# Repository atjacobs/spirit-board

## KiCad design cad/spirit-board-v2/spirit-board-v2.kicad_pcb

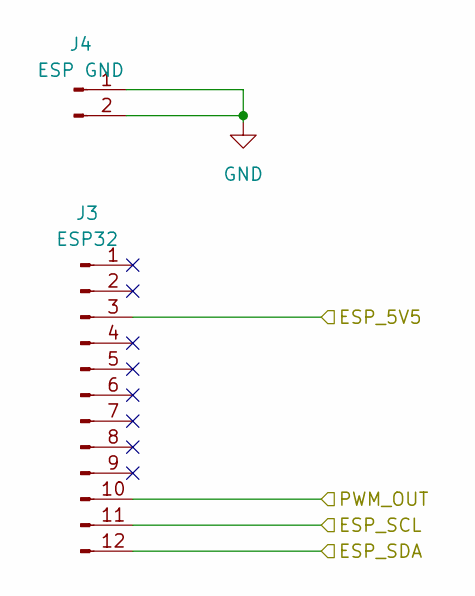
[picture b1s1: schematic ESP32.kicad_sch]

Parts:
J3: ESP32; PinHeader_1x12_P2.54mm_Vertical
J4: ESP GND; PinSocket_1x02_P2.54mm_Vertical

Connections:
/ESP32/ESP_5V5: J3.3; also elsewhere on the board
/ESP32/ESP_SCL: J3.11; also elsewhere on the board
/ESP32/ESP_SDA: J3.12; also elsewhere on the board
/ESP32/PWM_OUT: J3.10; also elsewhere on the board
GND: J4.1, J4.2; also elsewhere on the board

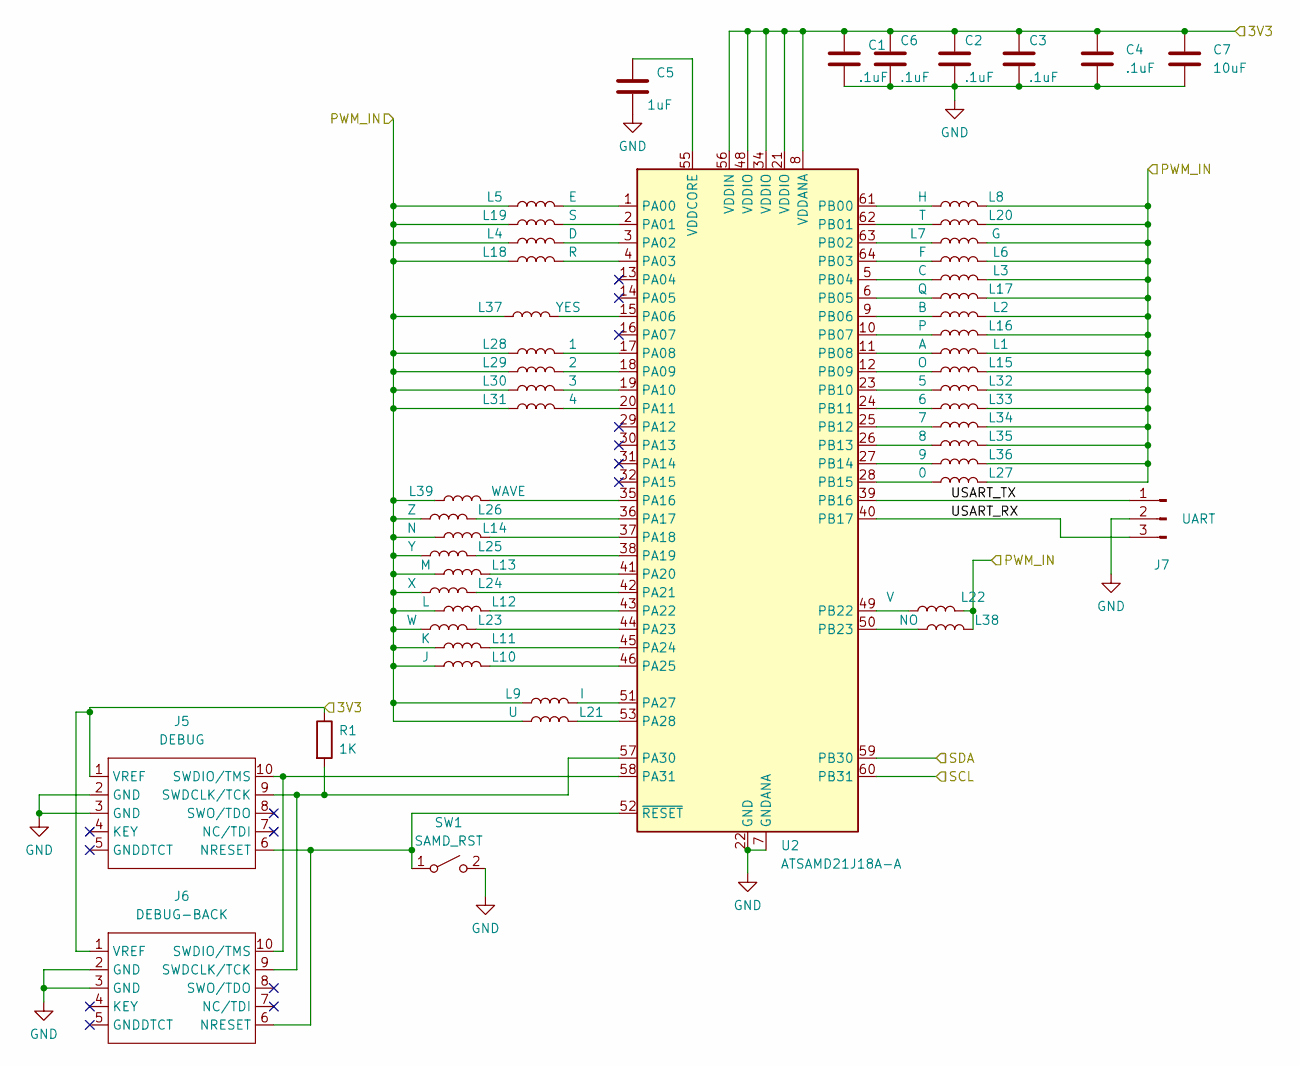
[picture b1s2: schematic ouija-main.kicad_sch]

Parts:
C1, C2, C3, C4, C6: .1uF; C_0805_2012Metric_Pad1.18x1.45mm_HandSolder
C5: 1uF; C_0805_2012Metric_Pad1.18x1.45mm_HandSolder
C7: 10uF; C_0805_2012Metric_Pad1.18x1.45mm_HandSolder
J5: DEBUG; Tag-Connect_TC2050-IDC-FP_2x05_P1.27mm_Vertical
J6: DEBUG-BACK; Tag-Connect_TC2050-IDC-FP_2x05_P1.27mm_Vertical
J7: UART; PinHeader_1x03_P2.54mm_Vertical
L1: A; AWCCA coil
L2: B; AWCCA coil
L3: C; AWCCA coil
L4: D; AWCCA coil
L5: E; AWCCA coil
L6: F; AWCCA coil
L7: G; AWCCA coil
L8: H; AWCCA coil
L9: I; AWCCA coil
L10: J; AWCCA coil
L11: K; AWCCA coil
L12: L; AWCCA coil
L13: M; AWCCA coil
L14: N; AWCCA coil
L15: O; AWCCA coil
L16: P; AWCCA coil
L17: Q; AWCCA coil
L18: R; AWCCA coil
L19: S; AWCCA coil
L20: T; AWCCA coil
L21: U; AWCCA coil
L22: V; AWCCA coil
L23: W; AWCCA coil
L24: X; AWCCA coil
L25: Y; AWCCA coil
L26: Z; AWCCA coil
L27: 0; AWCCA coil
L28: 1; AWCCA coil
L29: 2; AWCCA coil
L30: 3; AWCCA coil
L31: 4; AWCCA coil
L32: 5; AWCCA coil
L33: 6; AWCCA coil
L34: 7; AWCCA coil
L35: 8; AWCCA coil
L36: 9; AWCCA coil
L37: YES; AWCCA coil
L38: NO; AWCCA coil
L39: WAVE; AWCCA coil
R1: 1K; R_0805_2012Metric_Pad1.20x1.40mm_HandSolder
SW1: SAMD_RST; SW_Tactile_Straight_KSA0Axx1LFTR
U2: ATSAMD21J18A-A; TQFP64_10x10MC_MCH

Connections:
/ESP32/ESP_SCL: U2.60 (PB31); also elsewhere on the board
/ESP32/ESP_SDA: U2.59 (PB30); also elsewhere on the board
/ESP32/PWM_OUT: L1.1, L2.1, L3.1, L4.1, L5.1, L6.1, L7.2, L8.2, L9.2, L10.2, L11.2, L12.2, L13.2, L14.1, L15.1, L16.1, L17.1, L18.1, L19.1, L20.1, L21.2, L22.2, L23.2, L24.2, L25.2, L26.2, L27.1, L28.1, L29.1, L30.1, L31.1, L32.1, L33.1, L34.1, L35.1, L36.1, L37.1, L38.1, L39.2; also elsewhere on the board
/ouija-main/3V3: C1.1, C2.1, C3.1, C4.1, C6.1, C7.1, J5.1 (VREF), J6.1 (VREF), R1.1, U2.8 (VDDANA), U2.21 (VDDIO), U2.34 (VDDIO), U2.48 (VDDIO), U2.56 (VDDIN); also elsewhere on the board
/ouija-main/USART_RX: J7.3, U2.40 (PB17)
/ouija-main/USART_TX: J7.1, U2.39 (PB16)
GND: C1.2, C2.2, C3.2, C4.2, C5.2, C6.2, C7.2, J5.2 (GND), J5.3 (GND), J6.2 (GND), J6.3 (GND), J7.2, SW1.2 (B), U2.7 (GNDANA), U2.22 (GND), U2.33 (GND), U2.47 (GND), U2.54 (GND); also elsewhere on the board
unnamed: J5.6 (NRESET), J6.6 (NRESET), SW1.1 (A), U2.52 (~RESET)
unnamed: J5.9 (SWDCLK/TCK), J6.9 (SWDCLK/TCK), R1.2, U2.57 (PA30)
unnamed: J5.10 (SWDIO/TMS), J6.10 (SWDIO/TMS), U2.58 (PA31)
unnamed: L5.2, U2.1 (PA00)
unnamed: L19.2, U2.2 (PA01)
unnamed: L4.2, U2.3 (PA02)
unnamed: L18.2, U2.4 (PA03)
unnamed: L37.2, U2.15 (PA06)
unnamed: L28.2, U2.17 (PA08)
unnamed: L29.2, U2.18 (PA09)
unnamed: L30.2, U2.19 (PA10)
unnamed: L31.2, U2.20 (PA11)
unnamed: L39.1, U2.35 (PA16)
unnamed: L26.1, U2.36 (PA17)
unnamed: L14.2, U2.37 (PA18)
unnamed: L25.1, U2.38 (PA19)
unnamed: L13.1, U2.41 (PA20)
unnamed: L24.1, U2.42 (PA21)
unnamed: L12.1, U2.43 (PA22)
unnamed: L23.1, U2.44 (PA23)
unnamed: L11.1, U2.45 (PA24)
unnamed: L10.1, U2.46 (PA25)
unnamed: L9.1, U2.51 (PA27)
unnamed: L21.1, U2.53 (PA28)
unnamed: L8.1, U2.61 (PB00)
unnamed: L20.2, U2.62 (PB01)
unnamed: L7.1, U2.63 (PB02)
unnamed: L6.2, U2.64 (PB03)
unnamed: L3.2, U2.5 (PB04)
unnamed: L17.2, U2.6 (PB05)
unnamed: L2.2, U2.9 (PB06)
unnamed: L16.2, U2.10 (PB07)
unnamed: L1.2, U2.11 (PB08)
unnamed: L15.2, U2.12 (PB09)
unnamed: L32.2, U2.23 (PB10)
unnamed: L33.2, U2.24 (PB11)
unnamed: L34.2, U2.25 (PB12)
unnamed: L35.2, U2.26 (PB13)
unnamed: L36.2, U2.27 (PB14)
unnamed: L27.2, U2.28 (PB15)
unnamed: L22.1, U2.49 (PB22)
unnamed: L38.2, U2.50 (PB23)
unnamed: C5.1, U2.55 (VDDCORE)

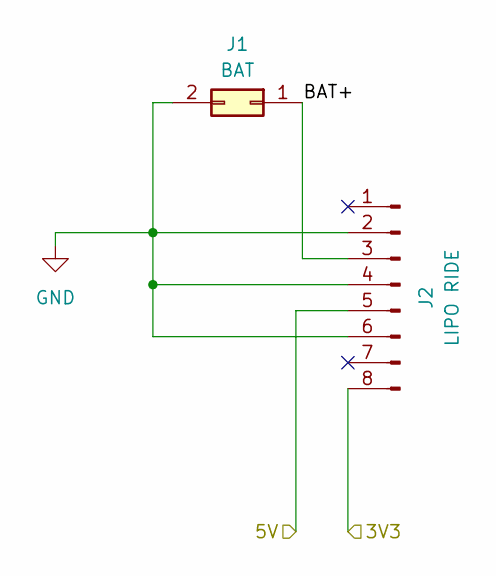
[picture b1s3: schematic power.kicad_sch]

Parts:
J1: BAT; PinSocket_2x01_P2.54mm_Vertical
J2: LIPO RIDE; PinSocket_1x08_P2.54mm_Vertical

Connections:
/ESP32/ESP_5V5: J2.5; also elsewhere on the board
/ouija-main/3V3: J2.8; also elsewhere on the board
/power/BAT+: J1.1, J2.3
GND: J1.2, J2.2, J2.4, J2.6; also elsewhere on the board

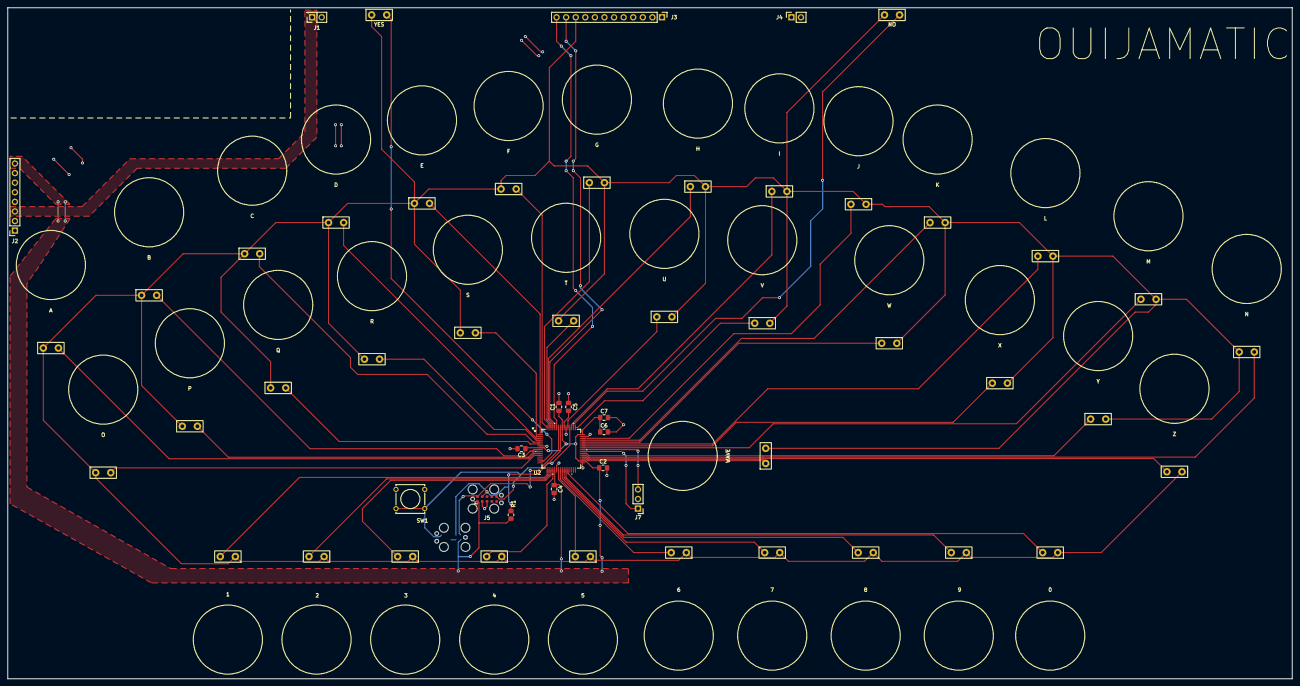
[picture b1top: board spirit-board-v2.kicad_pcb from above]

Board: 2 copper layers, 340.4 x 177.8 mm, 56 parts (1 on the bottom side), 52 nets.

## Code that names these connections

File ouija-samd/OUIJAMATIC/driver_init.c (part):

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{
	init_mcu();

	// GPIO on PA00

	// Set pin direction to input
	gpio_set_pin_direction(PIN_E, GPIO_DIRECTION_IN);
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
	gpio_set_pin_function(PIN_E, GPIO_PIN_FUNCTION_OFF);

	// GPIO on PA01

	// Set pin direction to input
	gpio_set_pin_direction(PIN_S, GPIO_DIRECTION_IN);
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
	gpio_set_pin_function(PIN_S, GPIO_PIN_FUNCTION_OFF);

	// GPIO on PA02

	// Set pin direction to input
	gpio_set_pin_direction(PIN_D, GPIO_DIRECTION_IN);
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
	gpio_set_pin_function(PIN_D, GPIO_PIN_FUNCTION_OFF);

	// GPIO on PA03

	// Set pin direction to input
	gpio_set_pin_direction(PIN_R, GPIO_DIRECTION_IN);
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
	gpio_set_pin_function(PIN_R, GPIO_PIN_FUNCTION_OFF);

	// GPIO on PA06

	// Set pin direction to input
	gpio_set_pin_direction(PIN_YES, GPIO_DIRECTION_IN);
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
	gpio_set_pin_function(PIN_YES, GPIO_PIN_FUNCTION_OFF);

	// GPIO on PA08

	// Set pin direction to input
	gpio_set_pin_direction(PIN_1, GPIO_DIRECTION_IN);
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
	gpio_set_pin_function(PIN_1, GPIO_PIN_FUNCTION_OFF);

	// GPIO on PA09

	// Set pin direction to input
	gpio_set_pin_direction(PIN_2, GPIO_DIRECTION_IN);
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
	gpio_set_pin_function(PIN_2, GPIO_PIN_FUNCTION_OFF);

	// GPIO on PA10

	// Set pin direction to input
	gpio_set_pin_direction(PIN_3, GPIO_DIRECTION_IN);
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
	gpio_set_pin_function(PIN_3, GPIO_PIN_FUNCTION_OFF);

	// GPIO on PA11

	// Set pin direction to input
	gpio_set_pin_direction(PIN_4, GPIO_DIRECTION_IN);
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
	gpio_set_pin_function(PIN_4, GPIO_PIN_FUNCTION_OFF);

	// GPIO on PA16

	// Set pin direction to input
	gpio_set_pin_direction(PIN_WAVE, GPIO_DIRECTION_IN);
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
	gpio_set_pin_function(PIN_WAVE, GPIO_PIN_FUNCTION_OFF);

	// GPIO on PA17

	// Set pin direction to input
	gpio_set_pin_direction(PIN_Z, GPIO_DIRECTION_IN);
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
	gpio_set_pin_function(PIN_Z, GPIO_PIN_FUNCTION_OFF);

	// GPIO on PA18

	// Set pin direction to input
	gpio_set_pin_direction(PIN_N, GPIO_DIRECTION_IN);
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
	gpio_set_pin_function(PIN_N, GPIO_PIN_FUNCTION_OFF);

	// GPIO on PA19

	// Set pin direction to input
	gpio_set_pin_direction(PIN_Y, GPIO_DIRECTION_IN);
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
	gpio_set_pin_function(PIN_Y, GPIO_PIN_FUNCTION_OFF);

	// GPIO on PA20

	// Set pin direction to input
	gpio_set_pin_direction(PIN_M, GPIO_DIRECTION_IN);
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
	gpio_set_pin_function(PIN_M, GPIO_PIN_FUNCTION_OFF);

	// GPIO on PA21

	// Set pin direction to input
	gpio_set_pin_direction(PIN_X, GPIO_DIRECTION_IN);
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
	gpio_set_pin_function(PIN_X, GPIO_PIN_FUNCTION_OFF);

	// GPIO on PA22

	// Set pin direction to input
	gpio_set_pin_direction(PIN_L, GPIO_DIRECTION_IN);
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
	gpio_set_pin_function(PIN_L, GPIO_PIN_FUNCTION_OFF);

	// GPIO on PA23

	// Set pin direction to input
	gpio_set_pin_direction(PIN_W, GPIO_DIRECTION_IN);
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
	gpio_set_pin_function(PIN_W, GPIO_PIN_FUNCTION_OFF);

	// GPIO on PA24

	// Set pin direction to input
	gpio_set_pin_direction(PIN_K, GPIO_DIRECTION_IN);
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
	gpio_set_pin_function(PIN_K, GPIO_PIN_FUNCTION_OFF);

	// GPIO on PA25

	// Set pin direction to input
	gpio_set_pin_direction(PIN_J, GPIO_DIRECTION_IN);
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
	gpio_set_pin_function(PIN_J, GPIO_PIN_FUNCTION_OFF);

	// GPIO on PA27

	// Set pin direction to input
	gpio_set_pin_direction(PIN_I, GPIO_DIRECTION_IN);
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
	gpio_set_pin_function(PIN_I, GPIO_PIN_FUNCTION_OFF);

	// GPIO on PA28

	// Set pin direction to input
	gpio_set_pin_direction(PIN_U, GPIO_DIRECTION_IN);
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
	gpio_set_pin_function(PIN_U, GPIO_PIN_FUNCTION_OFF);

	// GPIO on PB00

	// Set pin direction to input
	gpio_set_pin_direction(PIN_H, GPIO_DIRECTION_IN);
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
	gpio_set_pin_function(PIN_H, GPIO_PIN_FUNCTION_OFF);

	// GPIO on PB01

	// Set pin direction to input
	gpio_set_pin_direction(PIN_T, GPIO_DIRECTION_IN);
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
	gpio_set_pin_function(PIN_T, GPIO_PIN_FUNCTION_OFF);

	// GPIO on PB02

	// Set pin direction to input
	gpio_set_pin_direction(PIN_G, GPIO_DIRECTION_IN);
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
	gpio_set_pin_function(PIN_G, GPIO_PIN_FUNCTION_OFF);

	// GPIO on PB03

	// Set pin direction to input
	gpio_set_pin_direction(PIN_F, GPIO_DIRECTION_IN);
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
	gpio_set_pin_function(PIN_F, GPIO_PIN_FUNCTION_OFF);

	// GPIO on PB04

	// Set pin direction to input
	gpio_set_pin_direction(PIN_C, GPIO_DIRECTION_IN);
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
	gpio_set_pin_function(PIN_C, GPIO_PIN_FUNCTION_OFF);

	// GPIO on PB05

	// Set pin direction to input
	gpio_set_pin_direction(PIN_Q, GPIO_DIRECTION_IN);
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
	gpio_set_pin_function(PIN_Q, GPIO_PIN_FUNCTION_OFF);

	// GPIO on PB06

	// Set pin direction to input
	gpio_set_pin_direction(PIN_B, GPIO_DIRECTION_IN);
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
	gpio_set_pin_function(PIN_B, GPIO_PIN_FUNCTION_OFF);

	// GPIO on PB07

	// Set pin direction to input
	gpio_set_pin_direction(PIN_P, GPIO_DIRECTION_IN);
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
	gpio_set_pin_function(PIN_P, GPIO_PIN_FUNCTION_OFF);

	// GPIO on PB08

	// Set pin direction to input
	gpio_set_pin_direction(PIN_A, GPIO_DIRECTION_IN);
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
	gpio_set_pin_function(PIN_A, GPIO_PIN_FUNCTION_OFF);

	// GPIO on PB09

	// Set pin direction to input
	gpio_set_pin_direction(PIN_O, GPIO_DIRECTION_IN);
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
	gpio_set_pin_function(PIN_O, GPIO_PIN_FUNCTION_OFF);

	// GPIO on PB10

	// Set pin direction to input
	gpio_set_pin_direction(PIN_5, GPIO_DIRECTION_IN);
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
	gpio_set_pin_function(PIN_5, GPIO_PIN_FUNCTION_OFF);

	// GPIO on PB11

	// Set pin direction to input
	gpio_set_pin_direction(PIN_6, GPIO_DIRECTION_IN);
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
	gpio_set_pin_function(PIN_6, GPIO_PIN_FUNCTION_OFF);

	// GPIO on PB12

	// Set pin direction to input
	gpio_set_pin_direction(PIN_7, GPIO_DIRECTION_IN);
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
	gpio_set_pin_function(PIN_7, GPIO_PIN_FUNCTION_OFF);

	// GPIO on PB13

	// Set pin direction to input
	gpio_set_pin_direction(PIN_8, GPIO_DIRECTION_IN);
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
	gpio_set_pin_function(PIN_8, GPIO_PIN_FUNCTION_OFF);

	// GPIO on PB14

	// Set pin direction to input
	gpio_set_pin_direction(PIN_9, GPIO_DIRECTION_IN);
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
	gpio_set_pin_function(PIN_9, GPIO_PIN_FUNCTION_OFF);

	// GPIO on PB15

	// Set pin direction to input
	gpio_set_pin_direction(PIN_0, GPIO_DIRECTION_IN);
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
	gpio_set_pin_function(PIN_0, GPIO_PIN_FUNCTION_OFF);

	// GPIO on PB16

	// Set pin direction to input
	gpio_set_pin_direction(USART_TX, GPIO_DIRECTION_IN);

	gpio_set_pin_pull_mode(USART_TX,
	                       // <y> Pull configuration
	                       // <id> pad_pull_config
	                       // <GPIO_PULL_OFF"> Off
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	                       // <GPIO_PULL_DOWN"> Pull-down
	                       GPIO_PULL_OFF);

	gpio_set_pin_function(USART_TX, GPIO_PIN_FUNCTION_OFF);

	// GPIO on PB17

	// Set pin direction to input
	gpio_set_pin_direction(USART_RX, GPIO_DIRECTION_IN);

	gpio_set_pin_pull_mode(USART_RX,
	                       // <y> Pull configuration
	                       // <id> pad_pull_config
	                       // <GPIO_PULL_OFF"> Off
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	                       // <GPIO_PULL_DOWN"> Pull-down
	                       GPIO_PULL_OFF);

	gpio_set_pin_function(USART_RX, GPIO_PIN_FUNCTION_OFF);

	// GPIO on PB22

	// Set pin direction to input
	gpio_set_pin_direction(PIN_V, GPIO_DIRECTION_IN);
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
	gpio_set_pin_function(PIN_V, GPIO_PIN_FUNCTION_OFF);

	// GPIO on PB23

	// Set pin direction to input
	gpio_set_pin_direction(PIN_NO, GPIO_DIRECTION_IN);
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
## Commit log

2023-06-17 Mike's feedback
    - bypass caps on all power sources
    - Bulk cap on LED power
2023-06-19 per-coil schematic
2023-08-31 ouija board code
2023-09-11 ouija PCB mostly placed
    TODO:
    - lock MCU position
    - lock debug position
    - lock UARt position
    Considering increasing the board size. As-is, I can fit a smaller
    battery than I had been using, but I can't cover the "yes" and "no"
2023-09-19 Out to fab
2024-03-23 ouija v2
2024-03-24 samd ouija project added.
2024-11-17 changed GPIOs, enabled ble?
2024-11-17 added cadv2
